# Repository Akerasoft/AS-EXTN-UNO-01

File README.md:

# AS-EXTN-UNO-01
UNO Sheild for Exten Arcade project

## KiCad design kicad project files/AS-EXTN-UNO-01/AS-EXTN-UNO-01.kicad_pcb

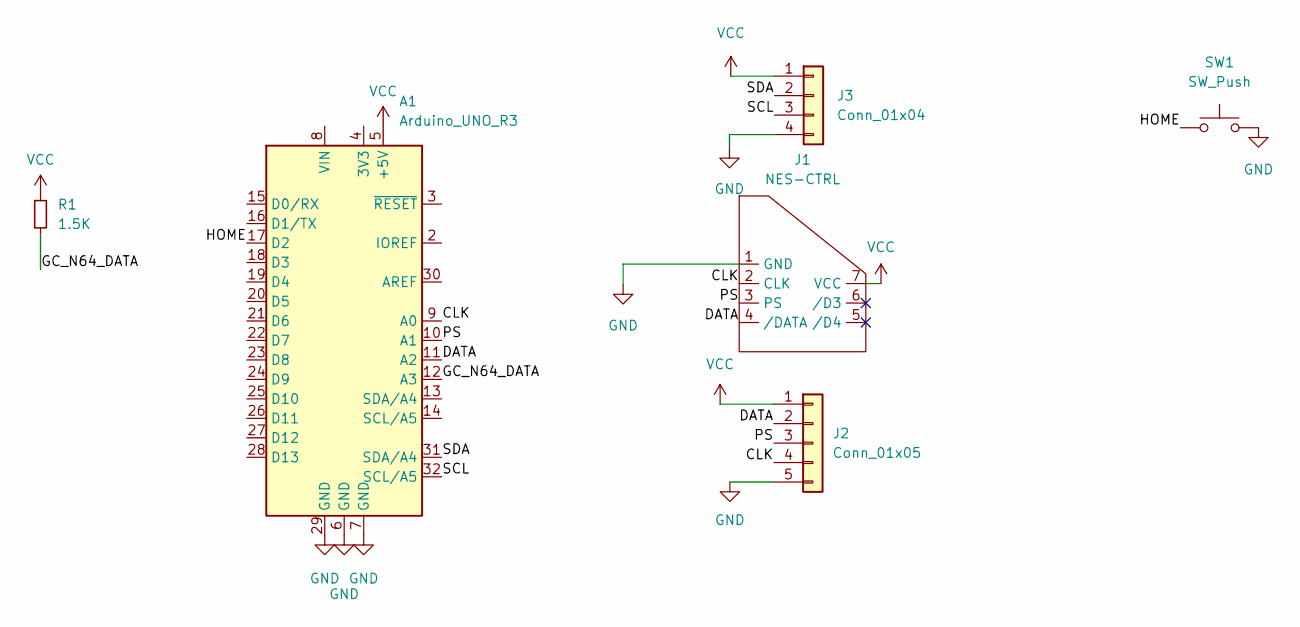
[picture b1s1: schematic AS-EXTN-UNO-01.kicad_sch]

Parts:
A1: Arduino_UNO_R3
J1: NES-CTRL; NES controller port 180
J2: Conn_01x05; JST_XH_B5B-XH-A_1x05_P2.50mm_Vertical
J3: Conn_01x04; JST_XH_B4B-XH-A_1x04_P2.50mm_Vertical
R1: 1.5K
SW1: SW_Push; SW_PUSH_6mm_H4.3mm

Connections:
/CLK: A1.9 (A0), J1.2 (CLK), J2.4
/DATA: A1.11 (A2), J1.4 (/DATA), J2.2
/GC_N64_DATA: A1.12 (A3), R1.2
/HOME: A1.17 (D2), SW1.1
/PS: A1.10 (A1), J1.3 (PS), J2.3
/SCL: A1.32 (SCL/A5), J3.3
/SDA: A1.31 (SDA/A4), J3.2
GND: A1.6 (GND), A1.7 (GND), A1.29 (GND), J1.1 (GND), J2.5, J3.4, SW1.2
VCC: A1.5 (+5V), J1.7 (VCC), J2.1, J3.1, R1.1

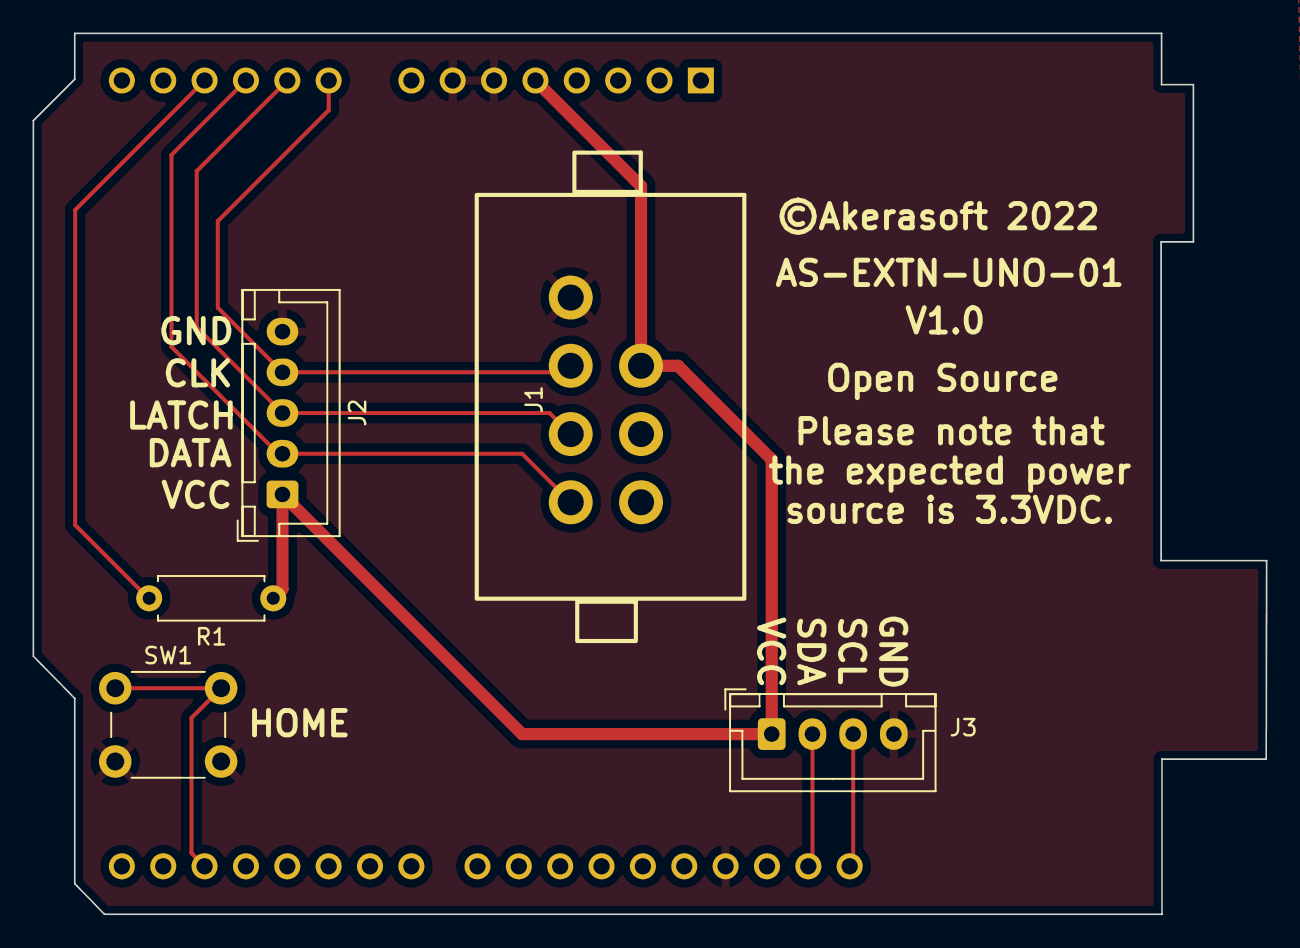
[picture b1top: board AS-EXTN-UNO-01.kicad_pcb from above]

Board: 2 copper layers, 75.7 x 54.1 mm, 6 parts (1 on the bottom side), 9 nets.

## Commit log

2022-11-27 Create LICENSE
2022-11-27 First attempt at PCB

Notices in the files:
kicad project files/AS-EXTN-UNO-01/AS-EXTN-UNO-01.kicad_pcb:
©Akerasoft 2022
kicad project files/AS-EXTN-UNO-01/AS-EXTN-UNO-01.kicad_sch:
License: Creative Commons Attribution 4.0 International Public License
